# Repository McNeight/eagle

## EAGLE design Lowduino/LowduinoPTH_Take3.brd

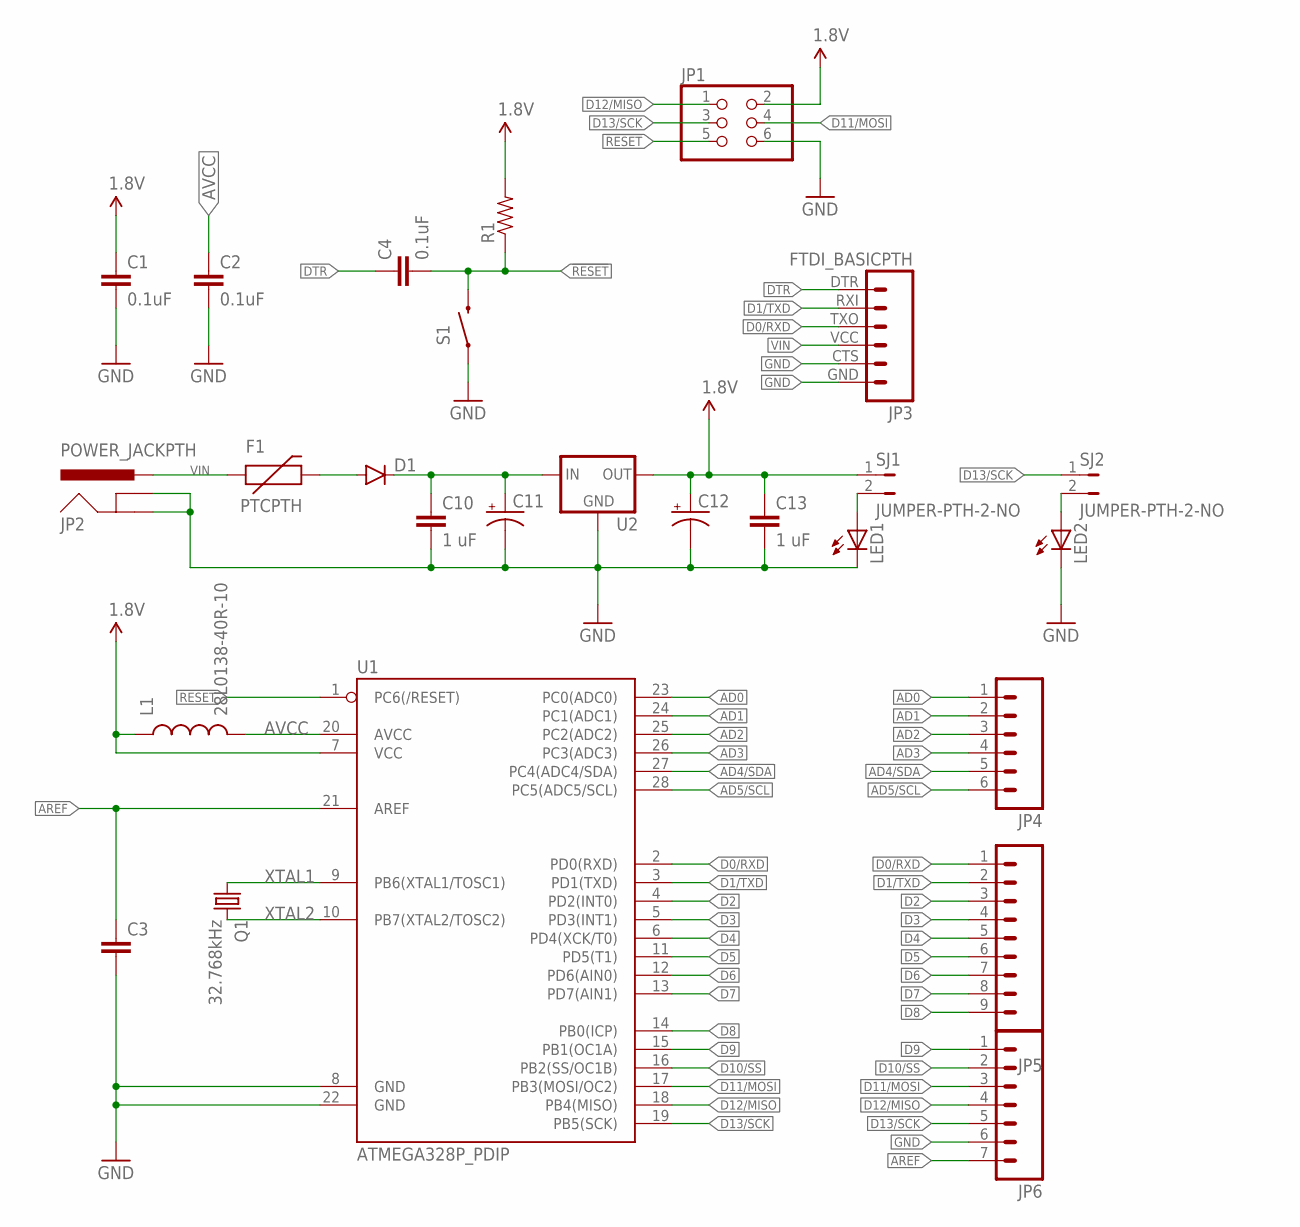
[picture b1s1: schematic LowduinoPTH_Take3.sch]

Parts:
C1, C4: 0.1uF; CAP-PTH-SMALL2
C2: 0.1uF; CAP-PTH-5MM
C3: CAPPTH2; CAP-PTH-SMALL2
C10, C13: 1 uF; CAP-PTH-SMALL2
C11, C12: CPOL-USE2.5-6; E2,5-6
D1: DIODEPTH; DIODE-1N4001
F1: PTCPTH; PTC
JP1: PINHD-2X3; 2X03
JP2: POWER_JACKPTH; POWER_JACK_PTH
JP3: FTDI_BASICPTH; FTDI_BASIC
JP4: M06SILK_FEMALE_PTH; 1X06
JP5: M09; 1X09
JP6: M07; 1X07
L1: 28L0138-40R-10; AXIAL-0.6
LED1, LED2: LED3MM
Q1: 32.768kHz; TC26V
R1: RESISTORPTH-1/4W-VERT; AXIAL-0.1
S1: SWITCH-MOMENTARY-2PTH; TACTILE-PTH
SJ1, SJ2: JUMPER-PTH-2-NO; PTH-JUMPER-2-NO_NO_SILK
U1: ATMEGA328P_PDIP; DIL28-3
U2: V_REG_78XXTO-92_UNTESTED; TO-92

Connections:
1.8V: C1.1, C12.+, C13.1, JP1.2, L1.P$1 (1), R1.P$2 (2), SJ1.1, U1.7 (VCC), U2.3 (OUT)
!RESET: C4.2, JP1.5, R1.P$1 (1), S1.3 (2), U1.1 (PC6(/RESET))
AD0: JP4.1, U1.23 (PC0(ADC0))
AD1: JP4.2, U1.24 (PC1(ADC1))
AD2: JP4.3, U1.25 (PC2(ADC2))
AD3: JP4.4, U1.26 (PC3(ADC3))
AD4/SDA: JP4.5, U1.27 (PC4(ADC4/SDA))
AD5/SCL: JP4.6, U1.28 (PC5(ADC5/SCL))
AREF: C3.1, JP6.7, U1.21 (AREF)
AVCC: C2.1, L1.P$2 (2), U1.20 (AVCC)
D0/RXD: JP3.TXO (3), JP5.1, U1.2 (PD0(RXD))
D1/TXD: JP3.RXI (2), JP5.2, U1.3 (PD1(TXD))
D2: JP5.3, U1.4 (PD2(INT0))
D3: JP5.4, U1.5 (PD3(INT1))
D4: JP5.5, U1.6 (PD4(XCK/T0))
D5: JP5.6, U1.11 (PD5(T1))
D6: JP5.7, U1.12 (PD6(AIN0))
D7: JP5.8, U1.13 (PD7(AIN1))
D8: JP5.9, U1.14 (PB0(ICP))
D9: JP6.1, U1.15 (PB1(OC1A))
D10/SS: JP6.2, U1.16 (PB2(SS/OC1B))
D11/MOSI: JP1.4, JP6.3, U1.17 (PB3(MOSI/OC2))
D12/MISO: JP1.1, JP6.4, U1.18 (PB4(MISO))
D13/SCK: JP1.3, JP6.5, SJ2.1, U1.19 (PB5(SCK))
DTR: C4.1, JP3.DTR (1)
GND: C1.2, C2.2, C3.2, C10.2, C11.-, C12.-, C13.2, JP1.6, JP2.GND, JP2.GNDBREAK, JP3.CTS (5), JP3.GND (6), JP6.6, LED1.K (C), LED2.K (C), S1.1, U1.8 (GND), U1.22 (GND), U2.1 (GND)
unnamed: LED1.A, SJ1.2
unnamed: LED2.A, SJ2.2
unnamed: D1.A, F1.P$2 (2)
unnamed: C10.1, C11.+, D1.C, U2.2 (IN)
VIN: F1.P$1 (1), JP2.PWR, JP3.VCC (4)
XTAL1: Q1.1, U1.9 (PB6(XTAL1/TOSC1))
XTAL2: Q1.2, U1.10 (PB7(XTAL2/TOSC2))

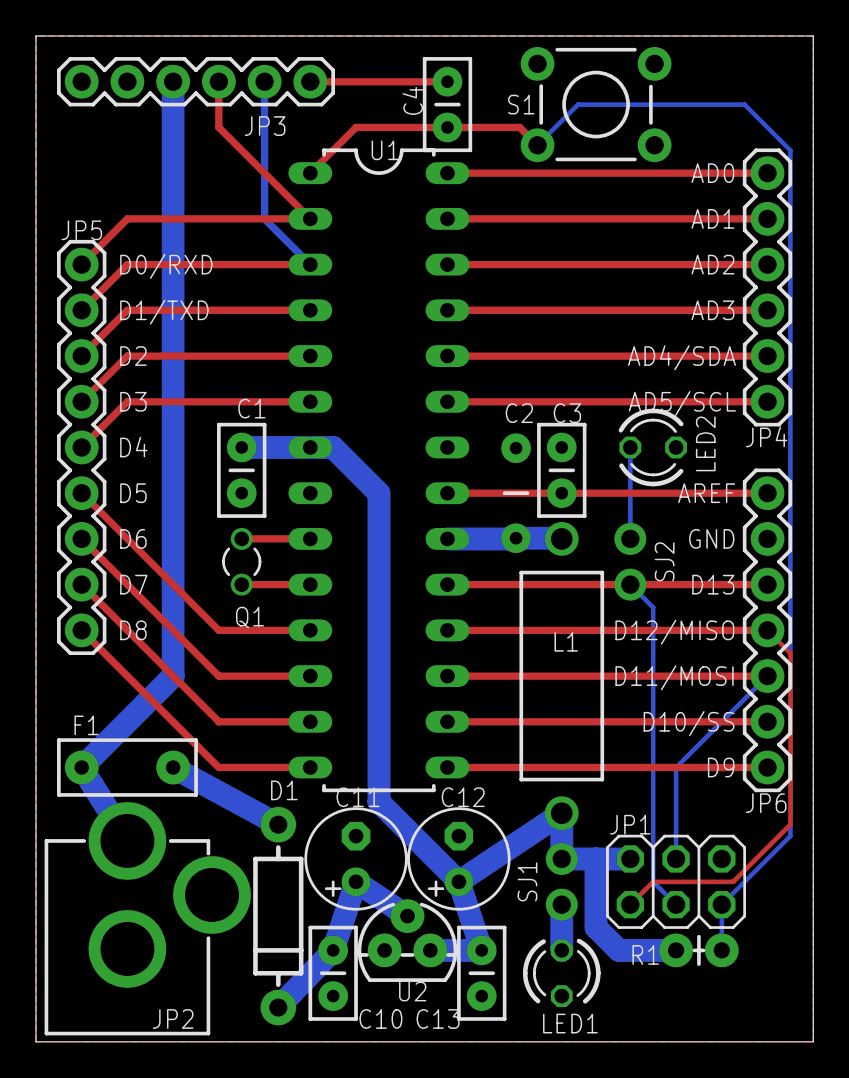
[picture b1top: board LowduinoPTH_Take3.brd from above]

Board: 2 copper layers, 43.2 x 55.9 mm, 26 parts (0 on the bottom side), 33 nets.

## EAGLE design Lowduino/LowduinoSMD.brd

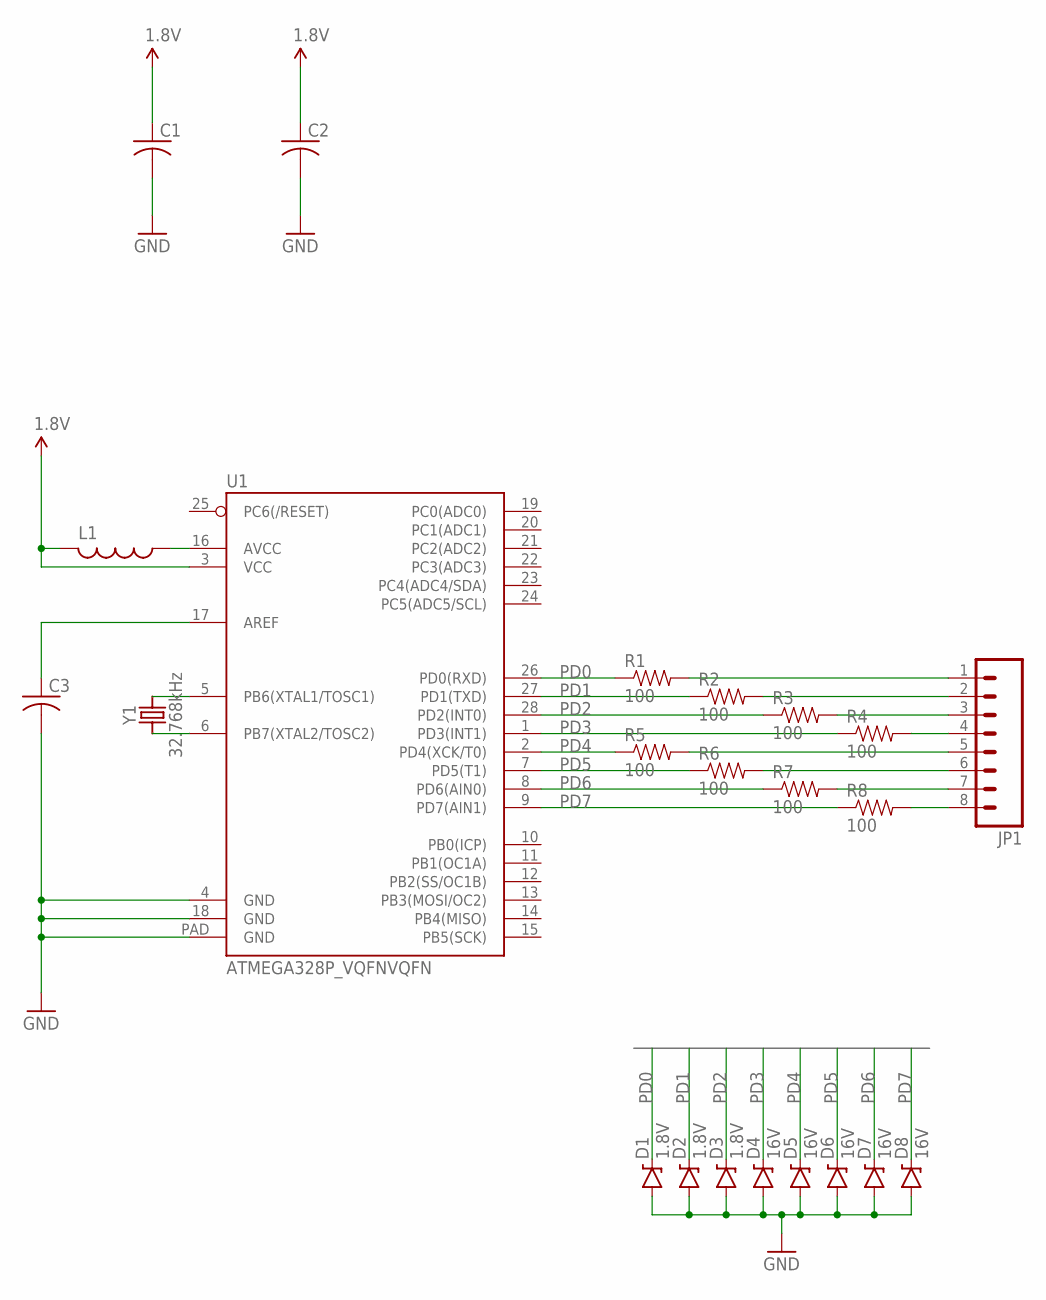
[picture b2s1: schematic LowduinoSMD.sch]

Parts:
C1, C3: C-USC0201; C0201
C2: C-USC0402; C0402
D1, D2, D3: 1.8V; SOD-123
D4, D5, D6, D7, D8: 16V; SOD-123
JP1: M08SILK_FEMALE_PTH; 1X08
L1: L-USL0201; L0201
R1, R2, R3, R4, R5, R6, R7, R8: 100; 0603-RES
U1: ATMEGA328P_VQFNVQFN; VQFN-28
Y1: 32.768kHz; 2-SMD

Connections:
1.8V: C1.1, C2.1, L1.2, U1.3 (VCC)
GND: C1.2, C2.2, C3.2, D1.A, D2.A, D3.A, D4.A, D5.A, D6.A, D7.A, D8.A, U1.4 (GND), U1.18 (GND), U1.PAD (GND)
unnamed: C3.1, U1.17 (AREF)
unnamed: L1.1, U1.16 (AVCC)
unnamed: U1.5 (PB6(XTAL1/TOSC1)), Y1.2
unnamed: U1.6 (PB7(XTAL2/TOSC2)), Y1.1
unnamed: JP1.1, R1.2
unnamed: JP1.2, R2.2
unnamed: JP1.3, R3.2
unnamed: JP1.4, R4.2
unnamed: JP1.5, R5.2
unnamed: JP1.6, R6.2
unnamed: JP1.7, R7.2
unnamed: JP1.8, R8.2
PD0: D1.C, R1.1, U1.26 (PD0(RXD))
PD1: D2.C, R2.1, U1.27 (PD1(TXD))
PD2: D3.C, R3.1, U1.28 (PD2(INT0))
PD3: D4.C, R4.1, U1.1 (PD3(INT1))
PD4: D5.C, R5.1, U1.2 (PD4(XCK/T0))
PD5: D6.C, R6.1, U1.7 (PD5(T1))
PD6: D7.C, R7.1, U1.8 (PD6(AIN0))
PD7: D8.C, R8.1, U1.9 (PD7(AIN1))

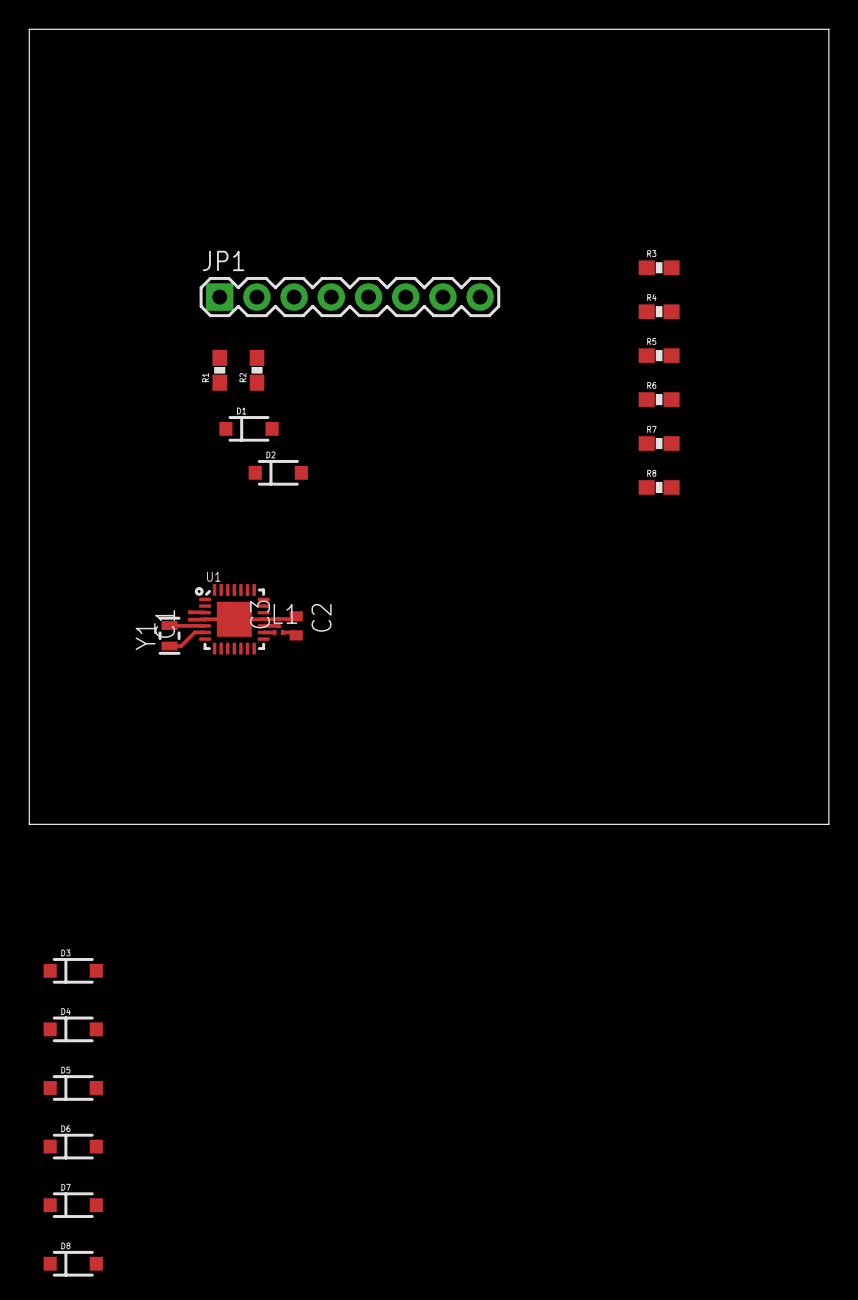
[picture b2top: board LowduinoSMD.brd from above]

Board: 2 copper layers, 54.6 x 54.3 mm, 23 parts (0 on the bottom side), 22 nets.

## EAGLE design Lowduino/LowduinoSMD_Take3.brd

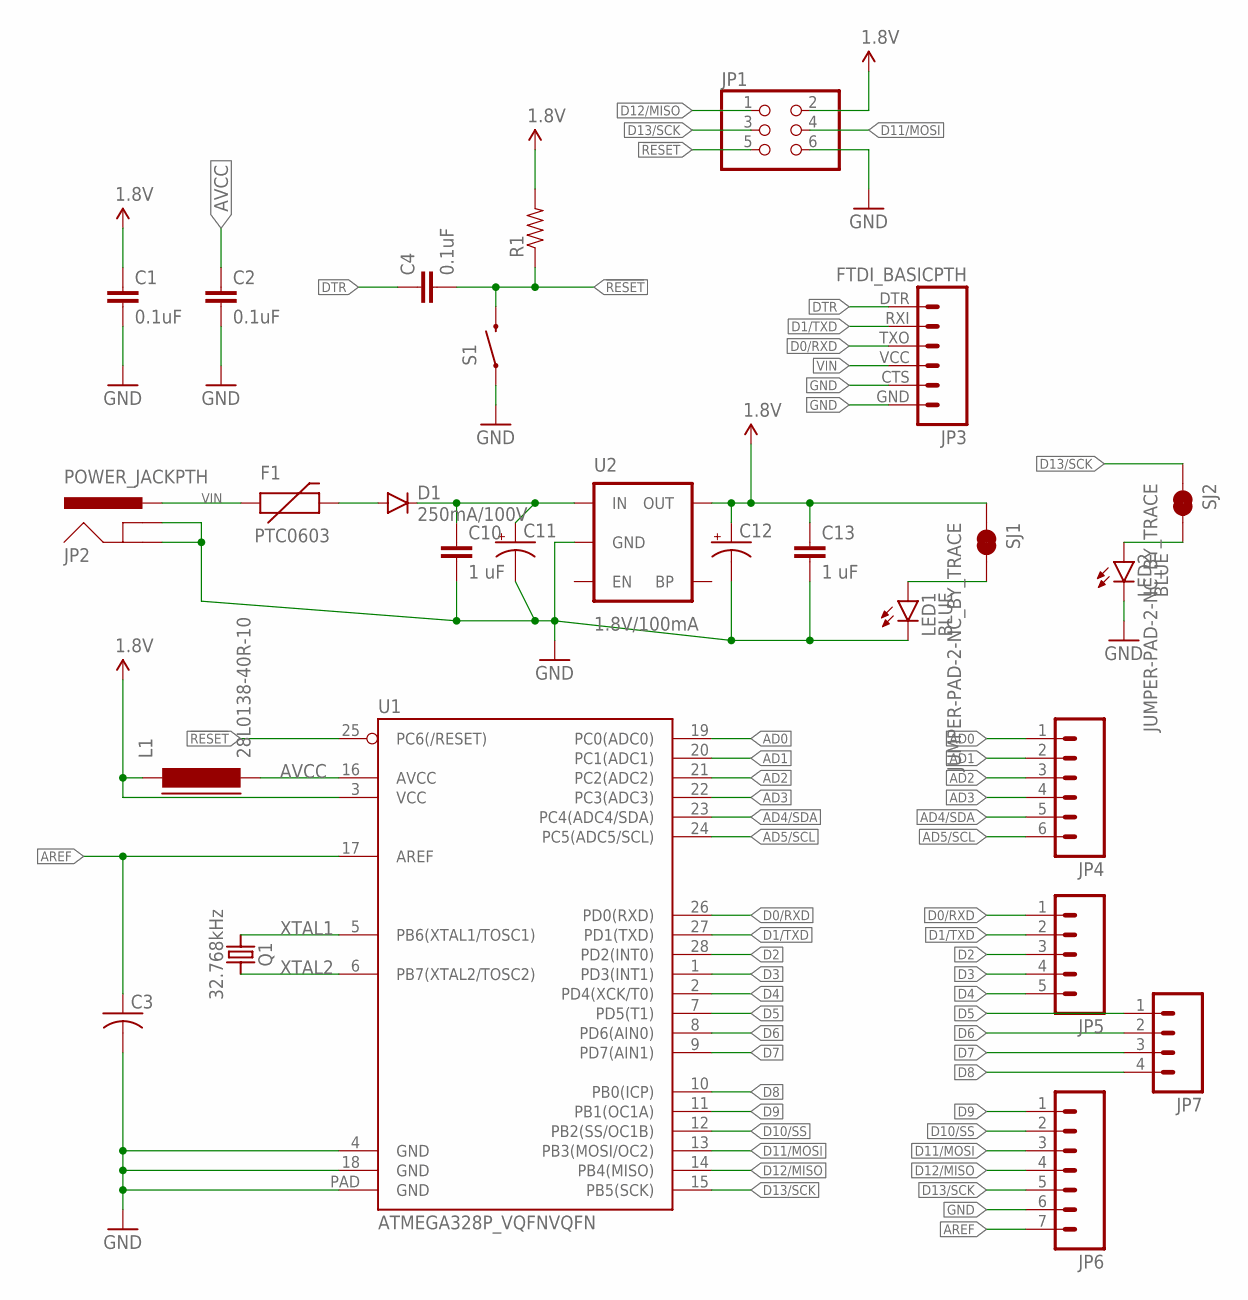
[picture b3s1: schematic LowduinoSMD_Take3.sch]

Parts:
C1, C2: 0.1uF; 0603-CAP
C3: C-US01005; C01005
C4: 0.1uF; 0402-CAP
C10, C13: 1 uF; 0402-CAP
C11, C12: CAP_POLC; PANASONIC_C
D1: 250mA/100V; SOD-323
F1: PTC0603; 0603
JP1: PINHD-2X3; 2X03
JP2: POWER_JACKPTH; POWER_JACK_PTH
JP3: FTDI_BASICPTH; FTDI_BASIC
JP4: M06SILK_FEMALE_PTH; 1X06
JP5: M05PTH; 1X05
JP6: M07; 1X07
JP7: M04PTH; 1X04
L1: 28L0138-40R-10; FB402
LED1, LED2: BLUE; LED-0603
Q1: 32.768kHz; 2-SMD
R1: RESISTOR0402; 0402-RES
S1: SWITCH-MOMENTARY-2SMD; TACTILE-SWITCH-SMD
SJ1, SJ2: JUMPER-PAD-2-NC_BY_TRACE; PAD-JUMPER-2-NC_BY_TRACE_YES_SILK
U1: ATMEGA328P_VQFNVQFN; VQFN-28
U2: 1.8V/100mA; SC70

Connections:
1.8V: C1.1, C12.+, C13.1, JP1.2, L1.1, R1.2, SJ1.1, U1.3 (VCC), U2.5 (OUT)
!RESET: C4.2, JP1.5, R1.1, S1.3 (2), U1.25 (PC6(/RESET))
AD0: JP4.1, U1.19 (PC0(ADC0))
AD1: JP4.2, U1.20 (PC1(ADC1))
AD2: JP4.3, U1.21 (PC2(ADC2))
AD3: JP4.4, U1.22 (PC3(ADC3))
AD4/SDA: JP4.5, U1.23 (PC4(ADC4/SDA))
AD5/SCL: JP4.6, U1.24 (PC5(ADC5/SCL))
AREF: C3.1, JP6.7, U1.17 (AREF)
AVCC: C2.1, L1.2, U1.16 (AVCC)
D0/RXD: JP3.TXO (3), JP5.1, U1.26 (PD0(RXD))
D1/TXD: JP3.RXI (2), JP5.2, U1.27 (PD1(TXD))
D2: JP5.3, U1.28 (PD2(INT0))
D3: JP5.4, U1.1 (PD3(INT1))
D4: JP5.5, U1.2 (PD4(XCK/T0))
D5: JP7.1, U1.7 (PD5(T1))
D6: JP7.2, U1.8 (PD6(AIN0))
D7: JP7.3, U1.9 (PD7(AIN1))
D8: JP7.4, U1.10 (PB0(ICP))
D9: JP6.1, U1.11 (PB1(OC1A))
D10/SS: JP6.2, U1.12 (PB2(SS/OC1B))
D11/MOSI: JP1.4, JP6.3, U1.13 (PB3(MOSI/OC2))
D12/MISO: JP1.1, JP6.4, U1.14 (PB4(MISO))
D13/SCK: JP1.3, JP6.5, SJ2.1, U1.15 (PB5(SCK))
DTR: C4.1, JP3.DTR (1)
GND: C1.2, C2.2, C3.2, C10.2, C11.-, C12.-, C13.2, JP1.6, JP2.GND, JP2.GNDBREAK, JP3.CTS (5), JP3.GND (6), JP6.6, LED1.C, LED2.C, S1.1, U1.4 (GND), U1.18 (GND), U1.PAD (GND), U2.2 (GND)
unnamed: LED1.A, SJ1.2
unnamed: LED2.A, SJ2.2
unnamed: D1.A, F1.2
unnamed: C10.1, C11.+, D1.C, U2.1 (IN)
VIN: F1.1, JP2.PWR, JP3.VCC (4)
XTAL1: Q1.1, U1.5 (PB6(XTAL1/TOSC1))
XTAL2: Q1.2, U1.6 (PB7(XTAL2/TOSC2))

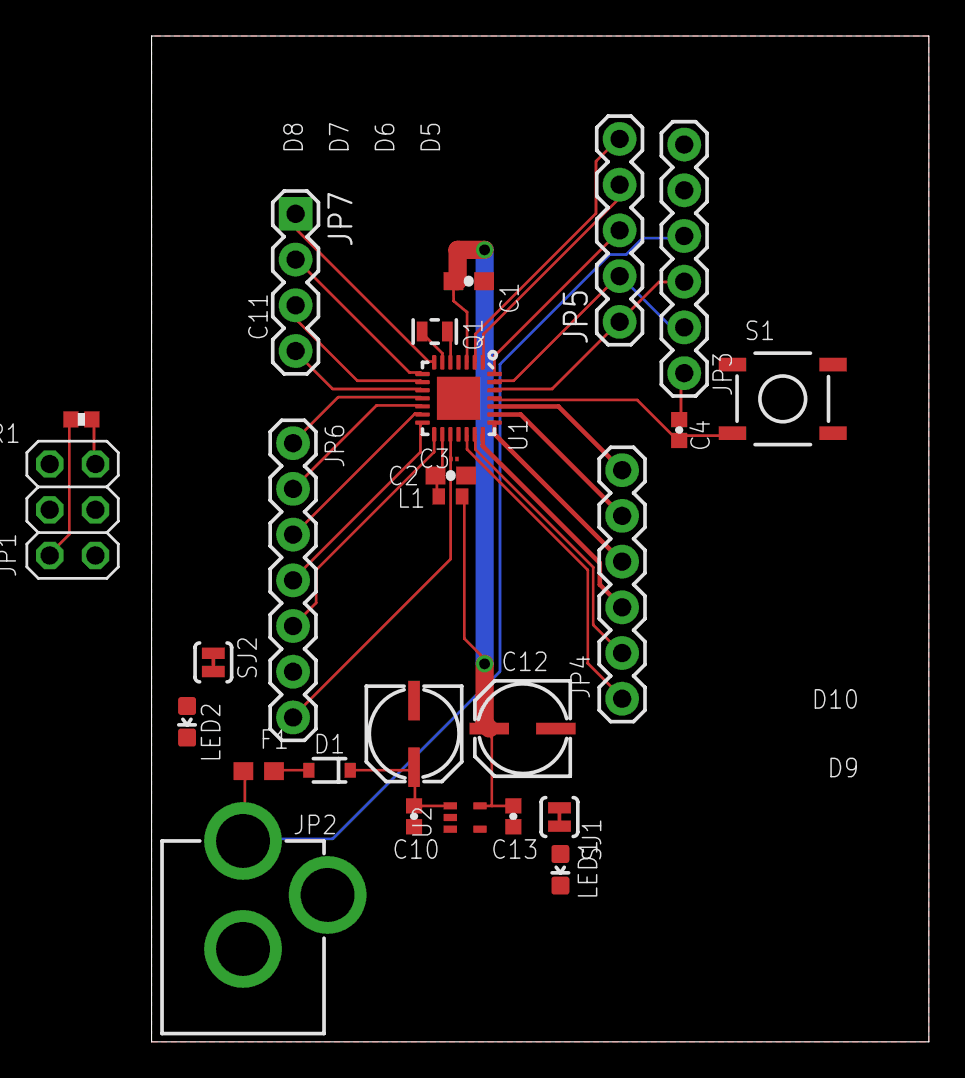
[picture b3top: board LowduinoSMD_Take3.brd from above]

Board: 2 copper layers, 43.2 x 55.9 mm, 27 parts (0 on the bottom side), 33 nets.

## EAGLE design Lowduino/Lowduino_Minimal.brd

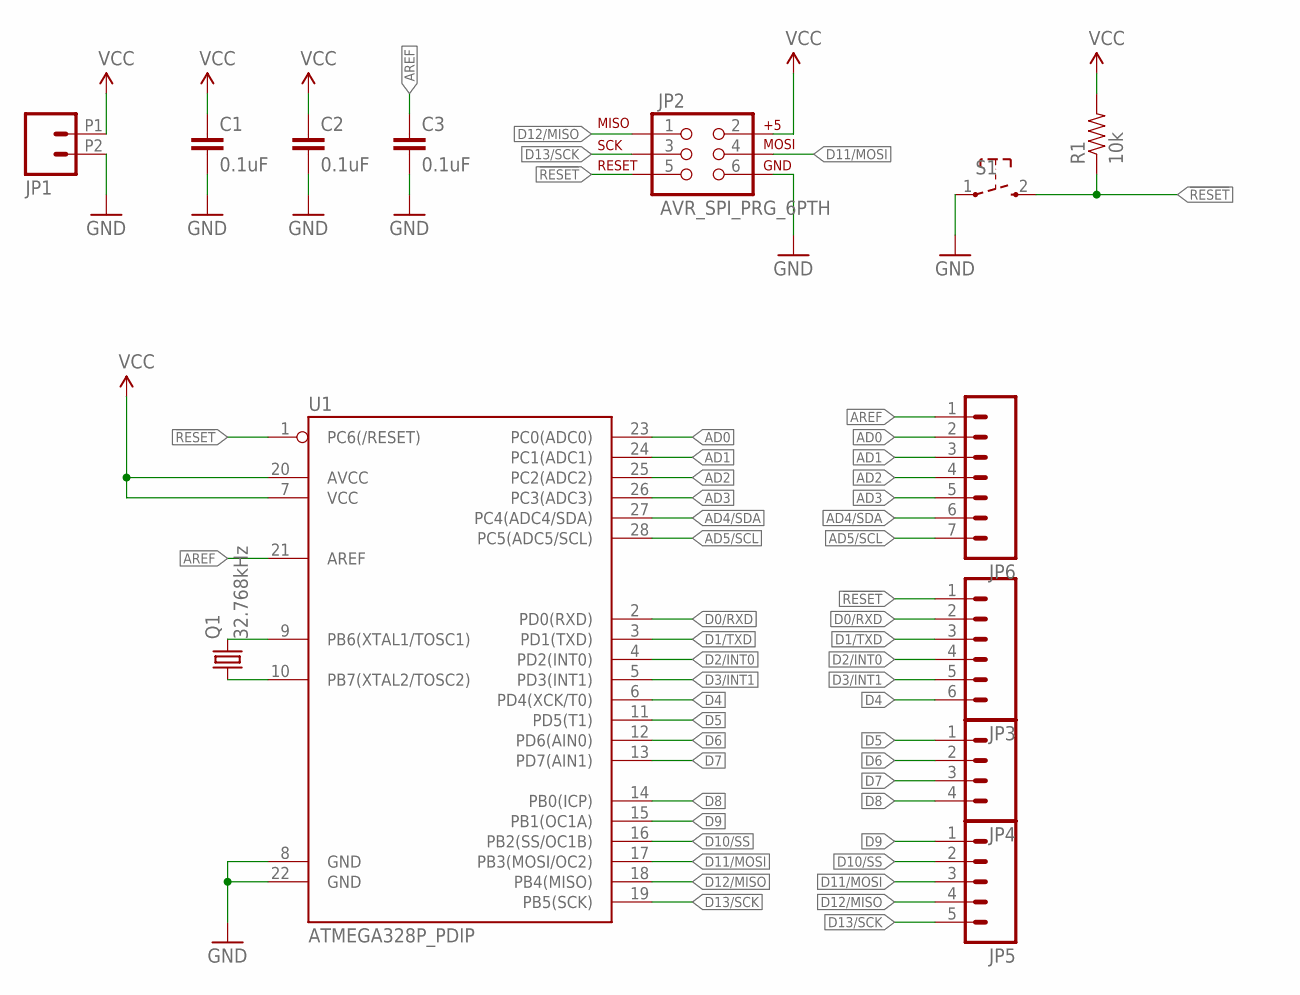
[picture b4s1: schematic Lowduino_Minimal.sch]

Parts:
C1, C2, C3: 0.1uF; CAP-PTH-SMALL
JP1: M022.54MM_SCREWTERM; 1X02_2.54_SCREWTERM
JP2: AVR_SPI_PRG_6PTH; 2X3
JP3: M06LOCK; 1X06_LOCK
JP4: M04LOCK; 1X04_LOCK
JP5: M05LOCK; 1X05_LOCK
JP6: M07LOCK; 1X07_LOCK
Q1: 32.768kHz; TC26V
R1: 10k; AXIAL-0.1
S1: MJTP_6MM; MJTP1243
U1: ATMEGA328P_PDIP; DIL28-3

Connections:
!RESET: JP2.5, JP3.1, R1.P$1 (1), S1.2 (3), U1.1 (PC6(/RESET))
AD0: JP6.2, U1.23 (PC0(ADC0))
AD1: JP6.3, U1.24 (PC1(ADC1))
AD2: JP6.4, U1.25 (PC2(ADC2))
AD3: JP6.5, U1.26 (PC3(ADC3))
AD4/SDA: JP6.6, U1.27 (PC4(ADC4/SDA))
AD5/SCL: JP6.7, U1.28 (PC5(ADC5/SCL))
AREF: C3.1, JP6.1, U1.21 (AREF)
D0/RXD: JP3.2, U1.2 (PD0(RXD))
D1/TXD: JP3.3, U1.3 (PD1(TXD))
D2/INT0: JP3.4, U1.4 (PD2(INT0))
D3/INT1: JP3.5, U1.5 (PD3(INT1))
D4: JP3.6, U1.6 (PD4(XCK/T0))
D5: JP4.1, U1.11 (PD5(T1))
D6: JP4.2, U1.12 (PD6(AIN0))
D7: JP4.3, U1.13 (PD7(AIN1))
D8: JP4.4, U1.14 (PB0(ICP))
D9: JP5.1, U1.15 (PB1(OC1A))
D10/SS: JP5.2, U1.16 (PB2(SS/OC1B))
D11/MOSI: JP2.4, JP5.3, U1.17 (PB3(MOSI/OC2))
D12/MISO: JP2.1, JP5.4, U1.18 (PB4(MISO))
D13/SCK: JP2.3, JP5.5, U1.19 (PB5(SCK))
GND: C1.2, C2.2, C3.2, JP1.P2 (2), JP2.6, S1.1, U1.8 (GND), U1.22 (GND)
VCC: C1.1, C2.1, JP1.P1 (1), JP2.2, R1.P$2 (2), U1.7 (VCC), U1.20 (AVCC)
XTAL1: Q1.2, U1.9 (PB6(XTAL1/TOSC1))
XTAL2: Q1.1, U1.10 (PB7(XTAL2/TOSC2))

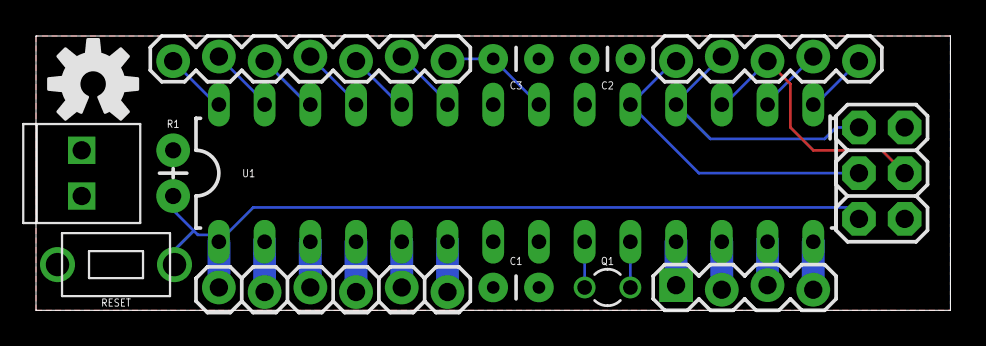
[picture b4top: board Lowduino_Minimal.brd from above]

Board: 2 copper layers, 50.8 x 15.2 mm, 14 parts (0 on the bottom side), 26 nets.

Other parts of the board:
U$2: OSHW-LOGO-M

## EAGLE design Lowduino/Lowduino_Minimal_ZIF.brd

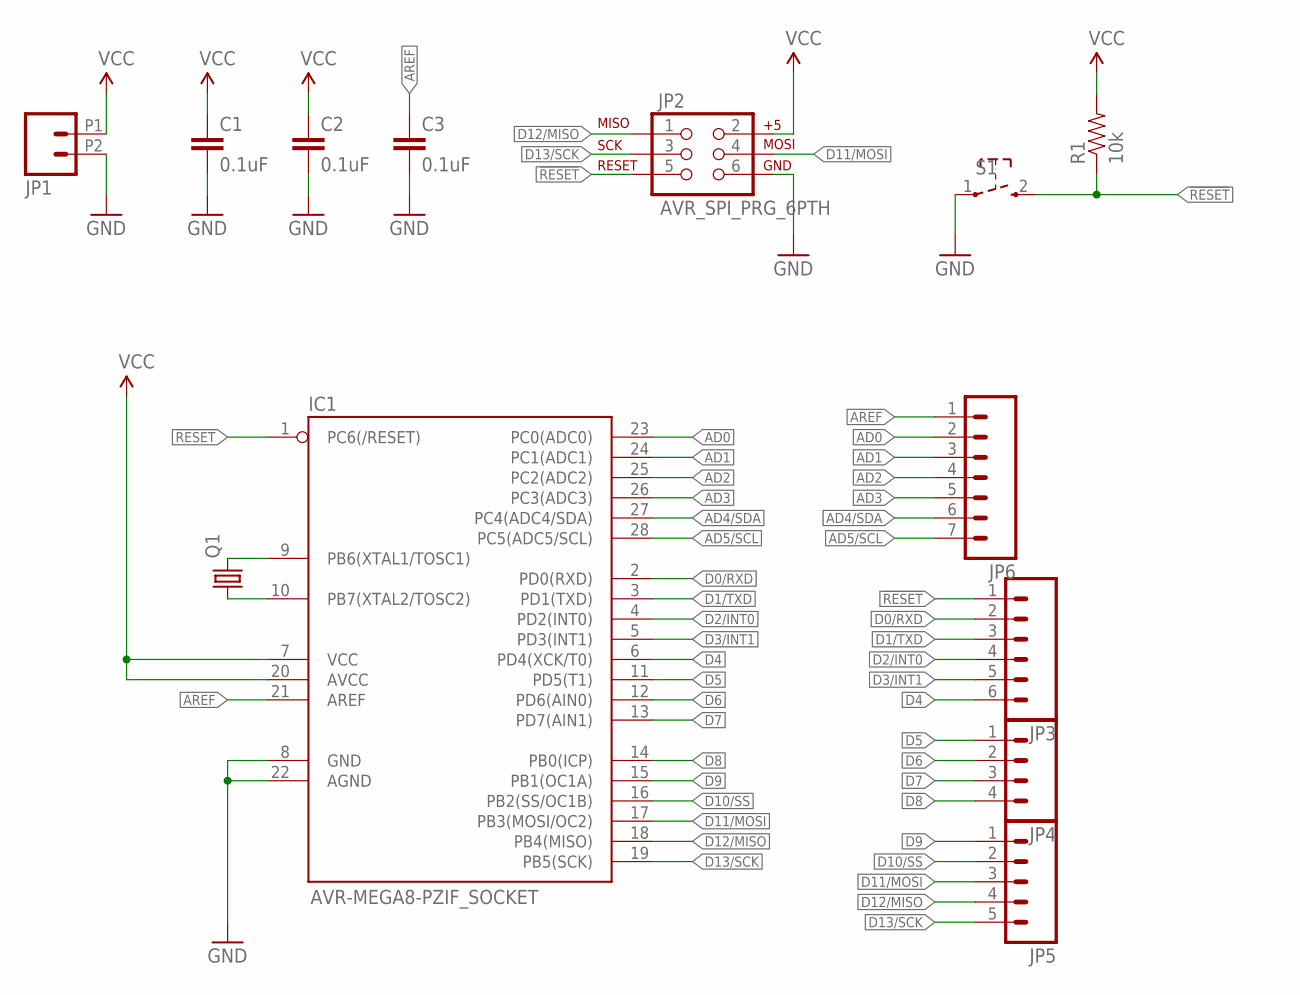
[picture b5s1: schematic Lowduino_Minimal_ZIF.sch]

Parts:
C1, C2, C3: 0.1uF; CAP-PTH-SMALL
IC1: AVR-MEGA8-PZIF_SOCKET; DIL28-3-ZIF_SOCKET
JP1: M022.54MM_SCREWTERM; 1X02_2.54_SCREWTERM
JP2: AVR_SPI_PRG_6PTH; 2X3
JP3: M06LOCK; 1X06_LOCK
JP4: M04LOCK; 1X04_LOCK
JP5: M05LOCK; 1X05_LOCK
JP6: M07LOCK; 1X07_LOCK
Q1: CRYSTALTC26V; TC26V
R1: 10k; AXIAL-0.1
S1: MJTP_6MM; MJTP1243

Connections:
!RESET: IC1.1 (PC6(/RESET)), JP2.5, JP3.1, R1.P$1 (1), S1.2 (3)
AD0: IC1.23 (PC0(ADC0)), JP6.2
AD1: IC1.24 (PC1(ADC1)), JP6.3
AD2: IC1.25 (PC2(ADC2)), JP6.4
AD3: IC1.26 (PC3(ADC3)), JP6.5
AD4/SDA: IC1.27 (PC4(ADC4/SDA)), JP6.6
AD5/SCL: IC1.28 (PC5(ADC5/SCL)), JP6.7
AREF: C3.1, IC1.21 (AREF), JP6.1
D0/RXD: IC1.2 (PD0(RXD)), JP3.2
D1/TXD: IC1.3 (PD1(TXD)), JP3.3
D2/INT0: IC1.4 (PD2(INT0)), JP3.4
D3/INT1: IC1.5 (PD3(INT1)), JP3.5
D4: IC1.6 (PD4(XCK/T0)), JP3.6
D5: IC1.11 (PD5(T1)), JP4.1
D6: IC1.12 (PD6(AIN0)), JP4.2
D7: IC1.13 (PD7(AIN1)), JP4.3
D8: IC1.14 (PB0(ICP)), JP4.4
D9: IC1.15 (PB1(OC1A)), JP5.1
D10/SS: IC1.16 (PB2(SS/OC1B)), JP5.2
D11/MOSI: IC1.17 (PB3(MOSI/OC2)), JP2.4, JP5.3
D12/MISO: IC1.18 (PB4(MISO)), JP2.1, JP5.4
D13/SCK: IC1.19 (PB5(SCK)), JP2.3, JP5.5
GND: C1.2, C2.2, C3.2, IC1.8 (GND), IC1.22 (AGND), JP1.P2 (2), JP2.6, S1.1
VCC: C1.1, C2.1, IC1.7 (VCC), IC1.20 (AVCC), JP1.P1 (1), JP2.2, R1.P$2 (2)
XTAL1: IC1.9 (PB6(XTAL1/TOSC1)), Q1.2
XTAL2: IC1.10 (PB7(XTAL2/TOSC2)), Q1.1

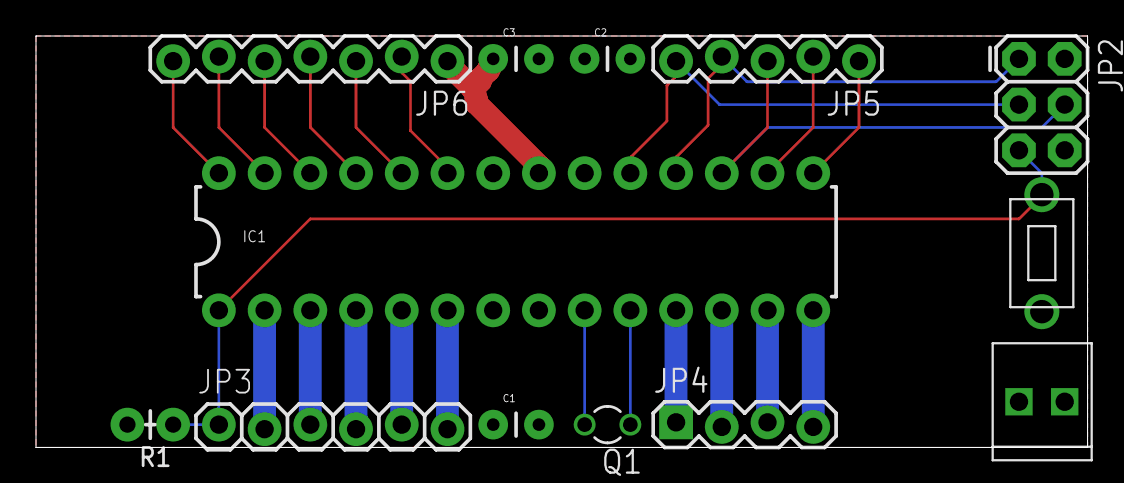
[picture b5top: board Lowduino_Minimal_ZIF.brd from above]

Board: 2 copper layers, 58.4 x 22.9 mm, 13 parts (0 on the bottom side), 26 nets.

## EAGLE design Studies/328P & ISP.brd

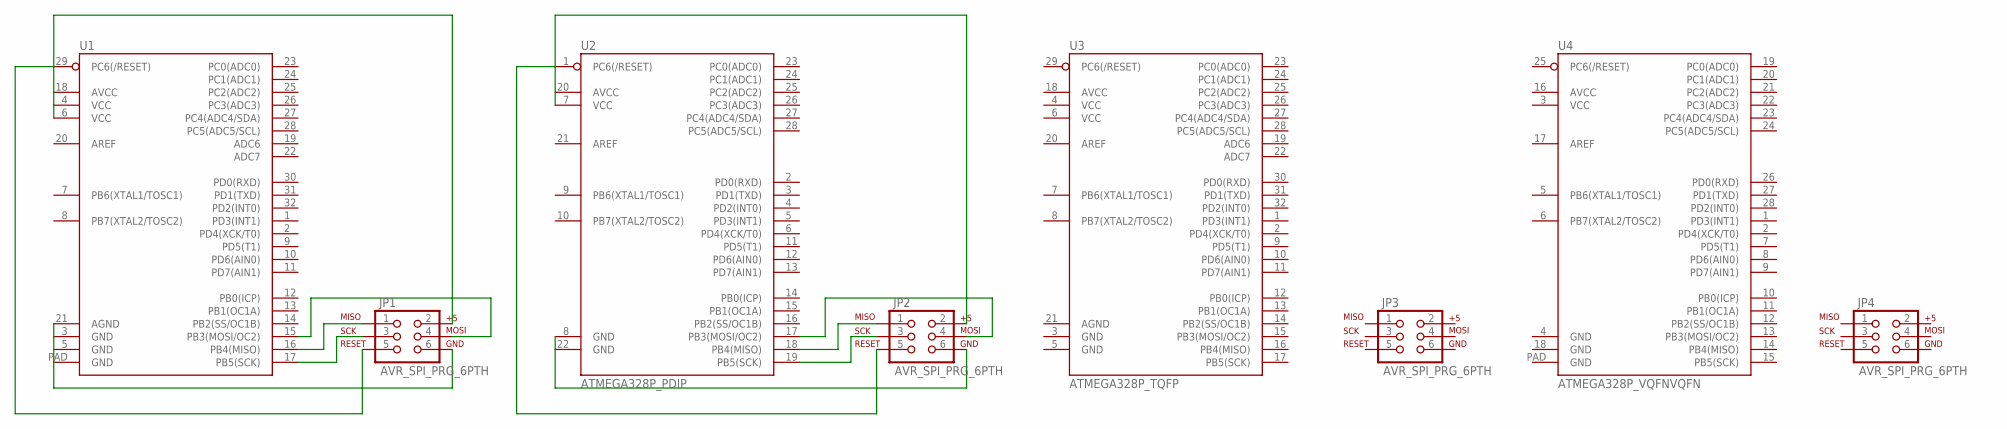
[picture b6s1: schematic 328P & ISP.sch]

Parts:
JP1, JP2, JP3, JP4: AVR_SPI_PRG_6PTH; 2X3
U1: ATMEGA328P_MLFMLF32; MLF32-PAD
U2: ATMEGA328P_PDIP; DIL28-3
U3: ATMEGA328P_TQFP; TQFP32-08
U4: ATMEGA328P_VQFNVQFN; VQFN-28

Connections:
unnamed: JP1.5, U1.29 (PC6(/RESET))
unnamed: JP1.3, U1.17 (PB5(SCK))
unnamed: JP1.1, U1.16 (PB4(MISO))
unnamed: JP1.4, U1.15 (PB3(MOSI/OC2))
unnamed: JP1.6, U1.3 (GND), U1.5 (GND), U1.21 (AGND), U1.PAD (GND)
unnamed: JP1.2, U1.4 (VCC), U1.6 (VCC), U1.18 (AVCC)
unnamed: JP2.5, U2.1 (PC6(/RESET))
unnamed: JP2.6, U2.8 (GND), U2.22 (GND)
unnamed: JP2.3, U2.19 (PB5(SCK))
unnamed: JP2.1, U2.18 (PB4(MISO))
unnamed: JP2.4, U2.17 (PB3(MOSI/OC2))
unnamed: JP2.2, U2.7 (VCC), U2.20 (AVCC)

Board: 2 copper layers, 8 parts (0 on the bottom side), 12 nets, no tracks yet.

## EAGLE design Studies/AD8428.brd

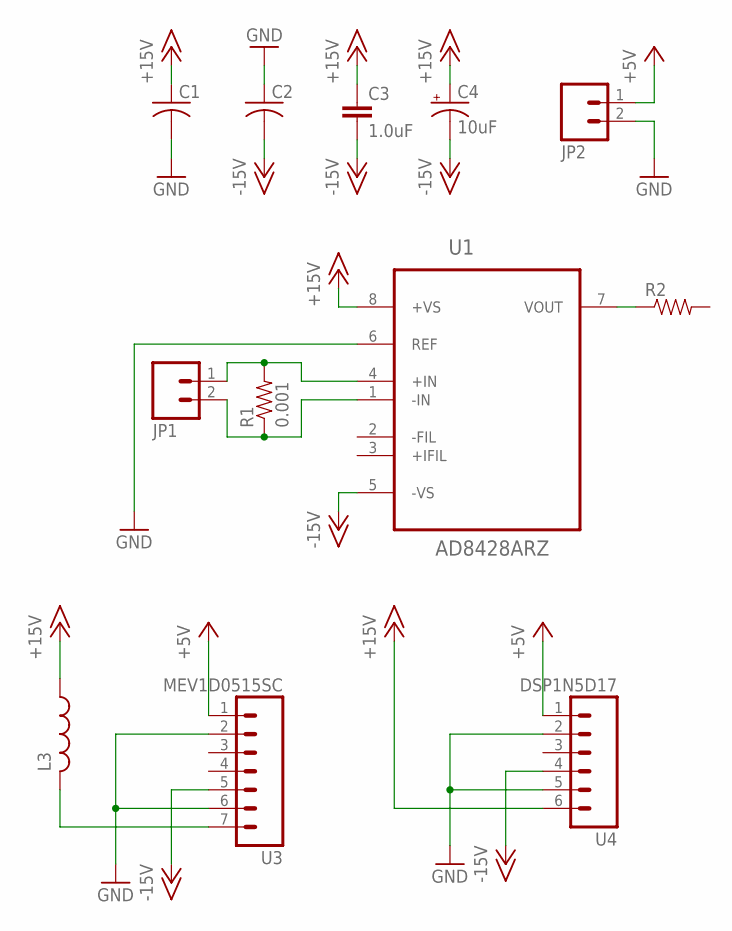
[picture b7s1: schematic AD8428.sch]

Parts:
C1, C2: C-USC0603; C0603
C3: 1.0uF; 1206
C4: 10uF; EIA3216
JP1, JP2: M025MM; SCREWTERMINAL-5MM-2
L3: L-USL2825P; L2825P
R1: 0.001; 2512
R2: RESISTOR0805-RES; 0805
U1: AD8428ARZ; SOIC127P600X175-8N
U3: MEV1D0515SC; 1X07
U4: DSP1N5D17; 1X06

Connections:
+5V: JP2.1, U3.1, U4.1
+15V: C1.1, C3.1, C4.A (+), L3.1, U1.8 (+VS), U4.6
+IN: JP1.1, R1.2, U1.4 (+IN)
-15V: C2.2, C3.2, C4.C (-), U1.5 (-VS), U3.5, U4.4
-IN: JP1.2, R1.1, U1.1 (-IN)
GND: C1.2, C2.1, JP2.2, U1.6 (REF), U3.2, U3.6, U4.2, U4.5
L3: L3.2, U3.7
VOUT: R2.1, U1.7 (VOUT)

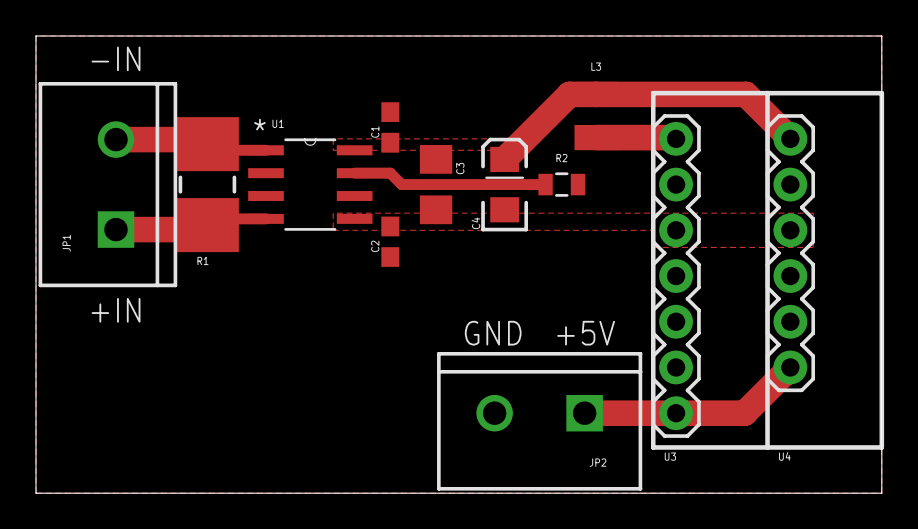
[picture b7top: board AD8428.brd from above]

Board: 2 copper layers, 47.0 x 25.4 mm, 12 parts (0 on the bottom side), 8 nets.

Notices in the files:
parts and their libraries:
SparkFun-Connectors: Licensing: Creative Commons ShareAlike 4.0 International - https://creativecommons.org/licenses/by-sa/4.0
